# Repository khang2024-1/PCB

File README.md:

View this project on [CADLAB.io](https://cadlab.io/project/30611). 

# PCB

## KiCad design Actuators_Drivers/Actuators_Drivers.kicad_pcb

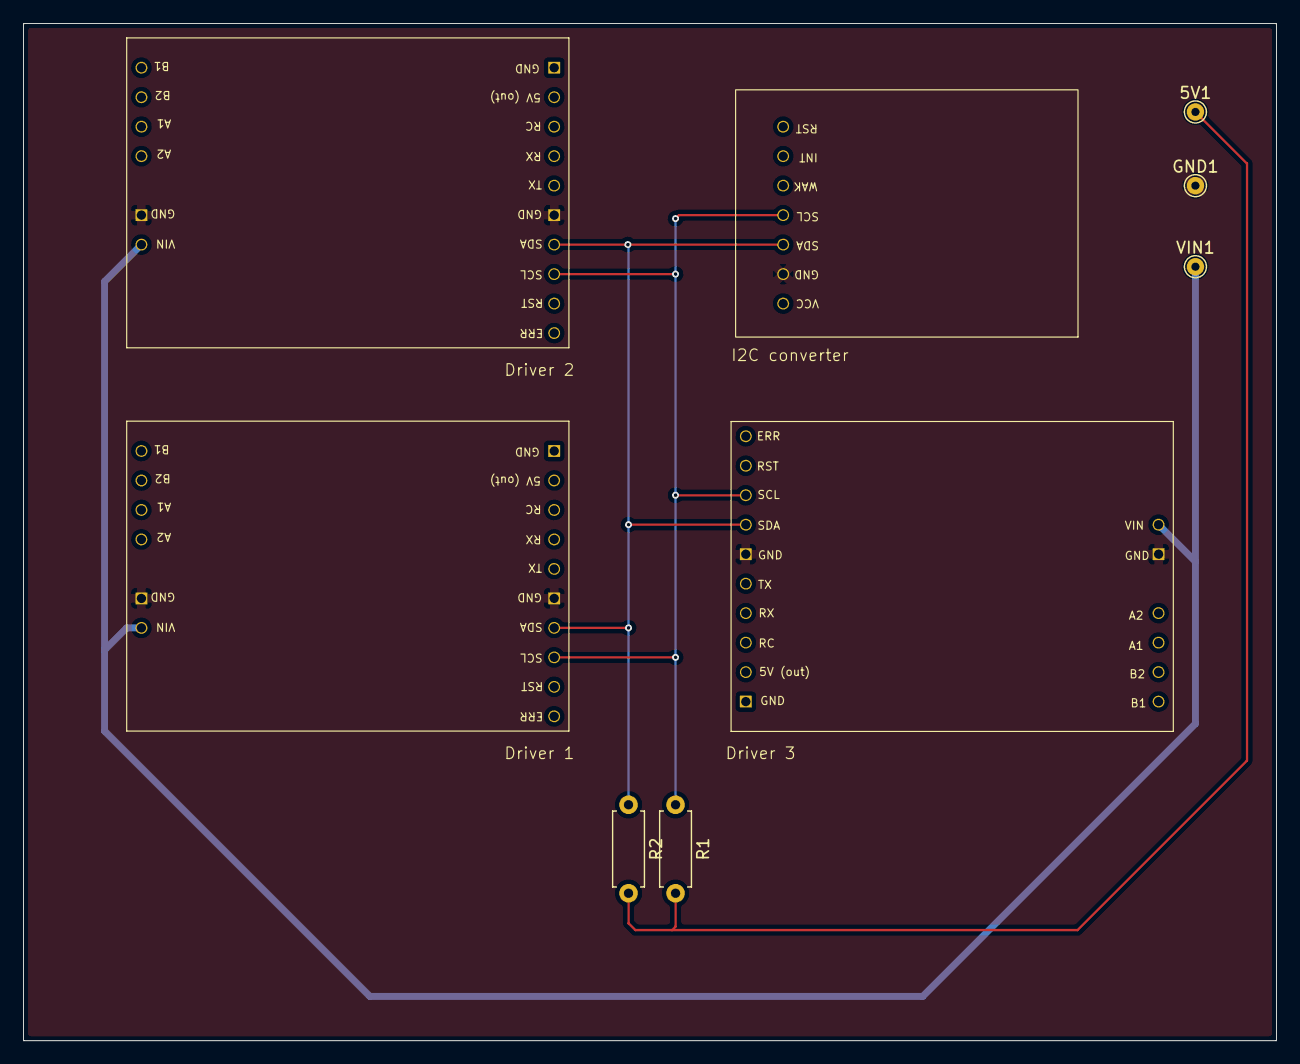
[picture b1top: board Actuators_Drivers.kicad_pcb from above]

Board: 2 copper layers, 108.0 x 87.6 mm, 9 parts (0 on the bottom side), 5 nets.

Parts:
5V1: 5V; TestPoint_THTPad_D1.5mm_Drill0.7mm
Driver 1, Driver 2, Driver 3: Tic_T500; Pololu_Tic_T500
GND1: GND; TestPoint_THTPad_D1.5mm_Drill0.7mm
I2C converter: CP2112_USB_I2C_connector; CP2112 _USB_I2C_connector
R1, R2: 2K; R_Axial_DIN0207_L6.3mm_D2.5mm_P7.62mm_Horizontal
VIN1: VIN; TestPoint_THTPad_D1.5mm_Drill0.7mm

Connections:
+15V: Driver 1.11 (VIN), Driver 2.11 (VIN), Driver 3.11 (VIN), VIN1.1 (1_1)
GND: Driver 1.5 (GND), Driver 1.12 (GND), Driver 2.5 (GND), Driver 2.12 (GND), Driver 3.5 (GND), Driver 3.12 (GND), GND1.1 (1_1), I2C converter.2 (GND)
unnamed: 5V1.1 (1_1), R1.2, R2.2
unnamed: Driver 1.3 (SCL), Driver 2.3 (SCL), Driver 3.3 (SCL), I2C converter.4 (SCL), R1.1
unnamed: Driver 1.4 (SDA), Driver 2.4 (SDA), Driver 3.4 (SDA), I2C converter.3 (SDA), R2.1
